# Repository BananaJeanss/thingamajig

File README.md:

# thingamajig

A board with 4 buttons and 4 leds that cycles through each led. When one or more buttons are pressed, only the specific leds corresponding to the pressed buttons are lit.

## Images

| Image                                                          | Description |
| -------------------------------------------------------------- | ----------- |
|           | PCB Front   |
|             | PCB Back    |
|         | Schematic   |
|  | PCB Design  |

---

Made for https://pathfinder.hackclub.com/

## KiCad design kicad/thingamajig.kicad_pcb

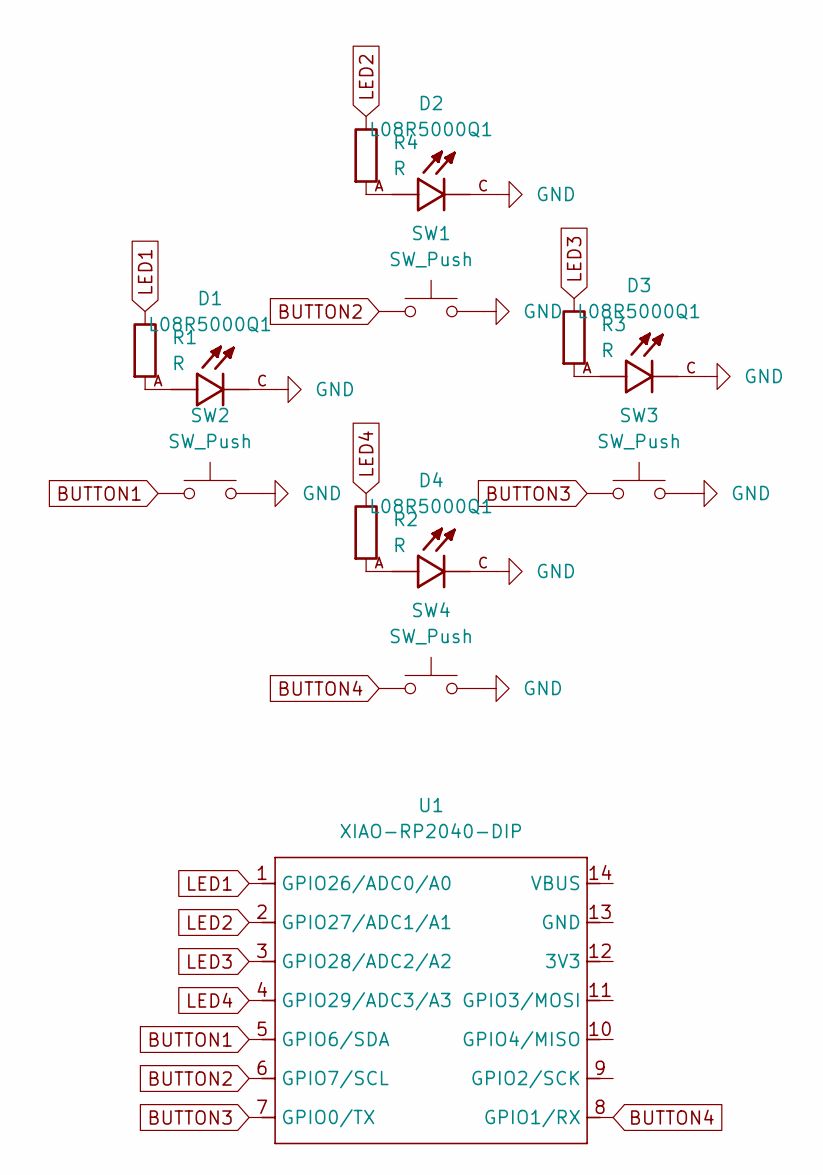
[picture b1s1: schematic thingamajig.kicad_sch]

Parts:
D1, D2, D3, D4: L08R5000Q1; LEDRD254W57D500H1070; PARTREV NA
R1, R2, R3, R4: R; R_Axial_DIN0204_L3.6mm_D1.6mm_P5.08mm_Horizontal
SW1, SW2, SW3, SW4: SW_Push; SW_Cherry_MX_1.00u_PCB
U1: XIAO-RP2040-DIP

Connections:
BUTTON1: SW2.1, U1.5 (GPIO6/SDA); also elsewhere on the board
BUTTON2: SW1.1, U1.6 (GPIO7/SCL); also elsewhere on the board
BUTTON3: SW3.1, U1.7 (GPIO0/TX); also elsewhere on the board
BUTTON4: SW4.1, U1.8 (GPIO1/RX); also elsewhere on the board
GND: D1.C, D2.C, D3.C, D4.C, SW1.2, SW2.2, SW3.2, SW4.2
LED1: R1.1, U1.1 (GPIO26/ADC0/A0); also elsewhere on the board
LED2: R4.1, U1.2 (GPIO27/ADC1/A1); also elsewhere on the board
LED3: R3.1, U1.3 (GPIO28/ADC2/A2); also elsewhere on the board
LED4: R2.1, U1.4 (GPIO29/ADC3/A3); also elsewhere on the board
unnamed: D1.A, R1.2
unnamed: D2.A, R4.2
unnamed: D3.A, R3.2
unnamed: D4.A, R2.2

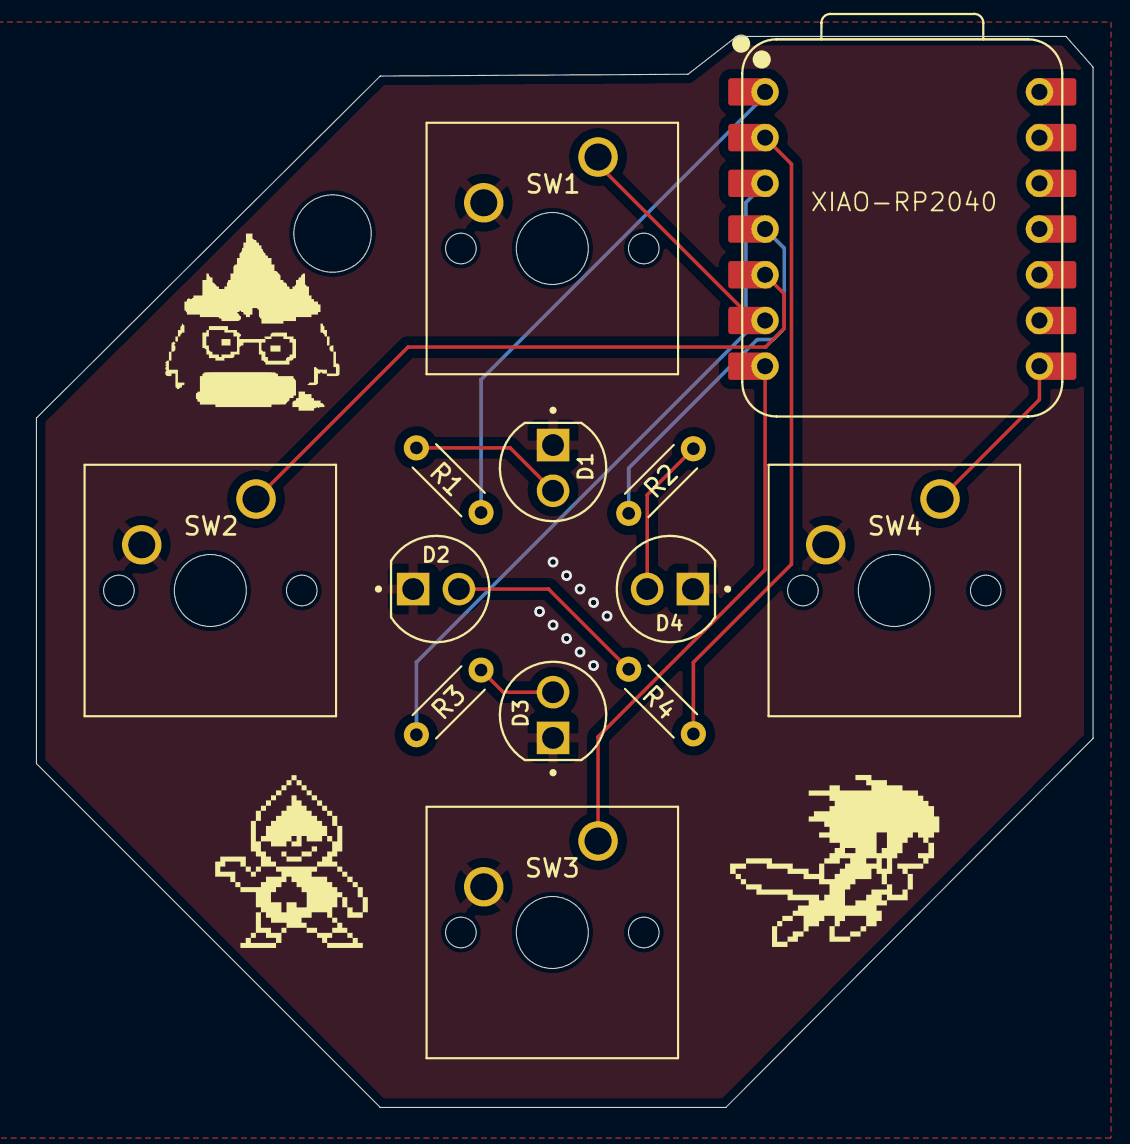
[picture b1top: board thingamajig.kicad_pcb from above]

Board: 2 copper layers, 58.7 x 59.5 mm, 13 parts (0 on the bottom side), 13 nets.

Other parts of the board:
XIAO-RP2040: XIAO-RP2040-DIP

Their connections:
BUTTON1: XIAO-RP2040.5 (GPIO6/SDA); also elsewhere on the board
BUTTON2: XIAO-RP2040.6 (GPIO7/SCL); also elsewhere on the board
BUTTON3: XIAO-RP2040.7 (GPIO0/TX); also elsewhere on the board
BUTTON4: XIAO-RP2040.8 (GPIO1/RX); also elsewhere on the board
LED1: XIAO-RP2040.1 (GPIO26/ADC0/A0); also elsewhere on the board
LED2: XIAO-RP2040.2 (GPIO27/ADC1/A1); also elsewhere on the board
LED3: XIAO-RP2040.3 (GPIO28/ADC2/A2); also elsewhere on the board
LED4: XIAO-RP2040.4 (GPIO29/ADC3/A3); also elsewhere on the board

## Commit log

2025-07-31 kicad files
2025-08-01 add arduino code
2025-08-01 add readme and images
